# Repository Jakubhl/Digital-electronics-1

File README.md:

# Digital-electronics-1

## Labs

### Header3
~~Scratch this.~~
**Source code**

```vhdl
architecture dataflow of gates is
begin
  f_o <= ((not b_i) and a_i)or ((not c_i) and (not b_i));
  found_o <=
  --fand_o <= a_i and b_i;
  --fxor_o <= a_i xor b_i;
and architecture dataflow;
```
https://www.vutbr.cz/

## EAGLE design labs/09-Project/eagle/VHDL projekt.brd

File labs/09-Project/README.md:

# Parkovací asistent
[Odkaz na GitHub](https://github.com/Dan5049/DE1-project)

### Členové týmu
Fabula Boris      [GitHub](https://github.com/bfbl/Digital-electronics-1)  
Havránek Daniel   [GitHub](https://github.com/Dan5049/Digital-electronics-1)   
Hlaváček Jakub    [GitHub](https://github.com/Jakubhl/Digital-electronics-1)   
Horna Aleš        [GitHub](https://github.com/xhorna16/Digital-electronics-1)

### Cíl projektu
<br>

* Cílem projektu je vytvoření parkovacího asistentu. Základní verze obsahuje jeden ultrazvukový senzor HC-SR04, bargrafem realizovaným pomocí LED integrovaných na desce a zvukuvou signalizací pomocí bzučáku.
* V druhé verzi projektu je plánováno nahradit LED optickou signalizaci externího bargrafu.
* V třetí verzi projektu je plánováno použití třech ultrazvukových senzorů namísto jednoho. Pro optickou signalizaci bude za potřebí využít třech bargrafů - každý pro jeden senzor. Zvuková signalizace pomocí bzučáku bude poté pro nejkritičtejší hodnotu.

## Popis hardwaru
### Blokové schéma

<br>

Na blokovém schématu můžeme vidět princip fungování. *Clock generator* nám generuje hodinový signál o frekvenci 100MHz, který je přiváděn do bloku *Trigger generator* a *Distance counter*. Další vstup do obou bloků je *reset*. 

Blok *Trigger generator* generuje řídící signál pro senzor *HC-SR04*. Tento signál je 10μs v hodnotě 1 a poté v hodnotě 0. Perioda tohoto signálu je 100ms.

Výstup ze senzoru *HC-SR04* je přiváděn do bloku *Distance counter* jako signál *echo*. Podle délky tohoto signálu je zjištěna vzdálenost od objektu. Podle vzdálenosti od objektu se rozsvítí určitý počet LED a nastaví se délka pípání bzučáku.

<br>

### DPS
#### Schéma zapojení přídavné desky

#### Náhled desky

<br>

Blok optické a akustické signalisace
* bargraf s 10 LED se spojenými katodami je přes předřadné odpory připojen na příslušné výstupy FPGA
* samokmitající bzučák, napájený z 5V, je spínán tranzistorem MOSFET, ovládaným z výstupu FPGA
* dále jsou obsaženy dva převodníky úrovní mezi 3,3V a 5V využité pro komunikaci mezi FPGA a ultrazvukovým snímačem
Převodníky úrovní
* řeší problém odlišných napětí odpovídajících logickým úrovním 1 na hlavní desce (s FPGA) a ultrazvukovém snímači
* jako zdroje napětí 3,3V a 5V použijí se příslušné výstupy na hlavní desce
* přenáší úroveň z jedné strany na druhou činností tranzistoru MOSFET
* vstup pro úroveň s určitým napětím označen jako I3, resp. I5, podle napětí
* výstup pro úroveň s určitým napětím označen jako O3, resp. O5, podle napětí
* vysvětlení funkce na příkladu:
	* na I3 je úroveň log. 0 (0V), T1 je otevřen (UGS=3,3V), úroveň 0 se tak přenese na výstup O5, kde bude napětí blízké nule (T1 otevřen)
	* na I3 je úroveň log. 1 (3,3V), T1 je uzavřen (UGS=0V), úroveň 1 se tak přenese na výstup O5, kde bude napětí 5V (T1 uzavřen)
	* funkce druhého převodníku je analogická
Praktické provedení
* většina součástek v provedení SMD, odpory-1206, tranzistory-SOT23, přesné informace v souboru "seznam-soucastek.txt"
* tranzistory jsou MOSFET, typ 2N7002, prahové napětí UGSth, povolený proud ID a další parametry jsou postačující
* jednostranná DPS, připojení k hlavní desce realisuje se pomocí páskových vodičů pájených do DPS bloku signalisace, na straně desky s FPGA připojeny pomocí vhodného konektoru
* na DPS vyznačena místa pro vyvrtání otvorů pro eventuální uchycení 4 šrouby M3
* bargraf může být osazen do patice DIL, což usnadní případnou výměnu za jiný typ (jiná barva světla)

Seznam součástek a osazovací plány na desku jsou na gitu ve složce *eagle*, popřípadě ve složce *images*

## VHDL moduly a simulace
### Modul *trigger*
``` VHDL
library ieee;               -- Standard library
use ieee.std_logic_1164.all;-- Package for data types and logic operations
use ieee.numeric_std.all;   -- Package for arithmetic operations

entity trigger is
port(
    clk     : in std_logic;    --clock
    rst     : in std_logic;    --reset
    trig_o  : out std_logic);  --trigger signal to sonar
end entity trigger;

architecture Behavioral of trigger is 
    signal s_tick     : integer; --time counter, one tick is 10ns
begin

    p_trigger : process(clk)is
    begin
        if rising_edge(clk) then
            if rst = '1' then                                       --if reset is 1, set trigger and time counter to 0
                trig_o <= '0'; 
                s_tick <= 0;           
            else
                if (s_tick <= 1000) then                            --set trrigger to 1 for time equal to 1000 ticks (10us)
                    trig_o <= '1';
                    s_tick <= s_tick + 1;
                elsif (s_tick < 10000000 and s_tick >= 1000) then   --set trigger to 0 for the rest of the time of 100ms
                    s_tick <= s_tick + 1;
                    trig_o <= '0';
                else 
                    s_tick <= 0;                                    --reset time counting
                end if;
           end if;
       end if;
    end process p_trigger;
end architecture Behavioral;
```
Modul *trigger* slouží ke generování budícího signálu *trig_o* pro senzor *HC-SR04*. Pokud je *reset* v hodnotě 1, budící signál *trig_o* je nastavený na hodnotu 0. V opačném případě se počítá počet nástupných hran hodinového signálu *clk* a ukládá se do pomocného signálu *s_tick*. Podle hodnoty pomocného signálu *s_tick* se nastavuje hodnota budícího signálu *trig_o* do hodnoty 0 nebo 1.

Hodnota uložená v pomocném signálu *s_tick* je čas v desítkách nanosekund. Pokud je hodnota pomocného signálu *s_tick* menší než 1000 (10μs), tak je nastavena hodnota budícího signálu *s_trig* na hodnotu 1. V opačném případě je nastavena na hodnotu 0. Pokud je hodnota pomocného signálu *s_tick* větší než 10000000 (100ms), tak dojde k vynulování pomocného signálu *s_tick*.

#### Simulace triggru

<br>

### Modul *dist*
``` VHDL
library ieee;               -- Standard library
use ieee.std_logic_1164.all;-- Package for data types and logic operations
use ieee.numeric_std.all;   -- Package for arithmetic operations

entity dist is
port(
    clk       : in std_logic;
    rst       : in std_logic;
    echo_i    : in std_logic;  --input from sonar
    buzz_o    : out std_logic; --output to buzzer
    leds_o    : out std_logic_vector (10 - 1 downto 0));
end entity dist;

architecture Behavioral of dist is 
    signal s_tick     : integer; --auxiliary variable for time counting
    signal s_dist     : integer; --auxiliary variable for distance counting
    signal s_tock     : integer; --auxiliary variable for time counting
    signal s_tock_on  : integer; --duty cycle for PWM signal to buzzer
    signal s_tock_off : integer; --period of the PWM signal
    signal s_xyz      : std_logic := '1'; --echo rising edge detection signal
begin

    p_distance : process(clk, echo_i)is --measure distance 
    begin
        if rising_edge(clk) then
            if rst = '1' then
                s_dist <= 1000; -- if dist = 1000 - error value (10m - more than it's able to measure)
                s_tick <= 0;
            else
                if echo_i = '1' then -- if echo is on 1, start counting time
                    s_tick <= s_tick +1; 
                    s_dist <= s_tick /(100*58); --conversion of ticks to distnace
                else
                    s_tick <= 0;
                end if;
            end if;
        end if;
    end process p_distance;
    
    p_bargraf : process (echo_i, s_dist, s_xyz)  --set the number of leds and duty cycle of buzzer
    begin
        if s_dist > 400 then
            leds_o <= "0000000000";
            s_tock_on <= 0;
            s_tock_off <= 100000000;
        end if; 
        if s_xyz = '1' and echo_i = '0' then
            if (s_dist <= 400 and s_dist >= 150) then --distance 4m to 1.5m
                leds_o <= "0000000001";
                s_tock_on <= 3000000;
                s_tock_off <= 10000000;
            elsif (s_dist < 150 and s_dist >= 100) then --distance 1.5m to 1m
                leds_o <= "0000000011";
                s_tock_on <= 3500000;
                s_tock_off <= 10000000;
            elsif (s_dist < 100 and s_dist >= 80) then --distance 1m to 0.8m
                leds_o <= "0000000111";
                s_tock_on <= 4000000;
                s_tock_off <= 10000000;
            elsif (s_dist < 80 and s_dist >= 70) then --distance 0.8m to 0.7m
                leds_o <= "0000001111";
                s_tock_on <= 4500000;
                s_tock_off <= 10000000; 
            elsif (s_dist < 70 and s_dist >= 60) then --distance 0.7m to 0.6m
                leds_o <= "0000011111";
                s_tock_on <= 5000000;
                s_tock_off <= 10000000;
            elsif (s_dist < 60 and s_dist >= 50) then --distance 0.6m to 0.5m
                leds_o <= "0000111111";
                s_tock_on <= 6000000;
                s_tock_off <= 10000000;
            elsif (s_dist < 50 and s_dist >= 40) then --distance 0.5m to 0.4m
                leds_o <= "0001111111";
                s_tock_on <= 7000000;
                s_tock_off <= 10000000;
            elsif (s_dist < 40 and s_dist >= 35) then --distance 0.4m to 0.35m
                leds_o <= "0011111111";
                s_tock_on <= 8000000;
                s_tock_off <= 10000000;
            elsif (s_dist < 35 and s_dist >= 30) then --distance 0.35m to 0.3m
                leds_o <= "0111111111";
                s_tock_on <= 9000000;
                s_tock_off <= 10000000;
            elsif s_dist < 30 then                      --distance less than 0.3m
                leds_o <= "1111111111";
                s_tock_on <= 3000000;
                s_tock_off <= 0;
            else
                leds_o <= "0000000000";
                s_tock_on <= 0;
                s_tock_off <= 100000000;
            end if;
       end if;
       s_xyz <= echo_i;    
    end process p_bargraf;
    
    p_buzz : process(clk, s_tock, s_tock_on, s_tock_off, echo_i)is
    begin                           -- controll buzzer based on the duty cycle values from p_bargraf
        if rising_edge(clk) then
            if rst = '1' then
                buzz_o <= '0';
                s_tock <= 0;
            else                
                if (s_tock <= s_tock_on) then
                    buzz_o <= '1';
                    s_tock <= s_tock + 1;
                elsif (s_tock <= s_tock_off and s_tock >= s_tock_on) then
                    buzz_o <= '0';
                    s_tock <= s_tock + 1;
                else 
                    s_tock <= 0;
                end if;
            end if;
        end if;    
    end process p_buzz;
    
end architecture Behavioral;
```
Modul *dist* slouží k získání hodnoty vzdálenosti od objektu a následému ovládání výstupních signalizací. Skládá se ze tří procesů: *p_distance*, *p_bargraf* a *p_buzz*.

Proces *p_distance* měří délku signálu *echo_i* přicházejícího ze senzoru *HC-SR04*. Stejně jak v modulu *trigger* se měří délka signálu *echo_i* na základě počtu náběžných hran hodinového signálu *clk*. Pokud je tedy hodnota signálu *echo_i* v hodnotě 1, počítá se počet náběžných hran signálu *clk* a ukládá se do pomocného signálu *s_tick*, který je stejně jak předtím v desítkách nanosekudn. Pokud je reset v hodnotě 1, dojde k vyresetování celého procesu a vzdálenost, uložená v pomocném signálu *s_dist*, se nastaví na hodnotu 10000. Tato hodnota odpovídá vzdálenosti 10m, což je hodnota vyšší, než je senzor schopen měřit - errorová hodnota. Jinak dochází k přepočtu délky signálu *echo_i* na vzdálenost, která se následně ukládá do pomocného signálu *s_dist*. Přepočet je uveden v datasheetu k senzoru *HC-SR04* - čas v mikrosekudnách děleno 58 je roven vzdálenosti v centimetrech.

V procesu *p_bargraf* dochází k zapnutí určitého počtu LED, v závislosti na vzdálenosti (hodnota signálu *s_dist*). Počet rozsvícených LED není přímo úměrný vzdálenosti - pro větší vzdálenosti je odstup mezi jednotlivými LED větší než pro kratší vzdálenosti. Všechny LED svítí při vzdálenosti menší 30cm. Také se v tomto procesu nastavuje střída a perioda pro signál *s_buzz*, který spouští zvukovou signalizaci. Perioda signálu *s_buzz* je 100ms, střída se mění v závislosti na vzdálenosti a nastavuje se spolu s LED.

V procesu *p_buzz* dochází ke generování signálu pro zvukovou signalizaci *s_buzz* v závisloti na hodnotách získaných v předchozím procesu. Pokud je vzdálenost od objektu menší než 30cm, je signál *s_buzz* nastaven na hodnotu 1 a nemění se. Čím je vzdálenost větší, tím kratší dobu je signál *s_buzz* nastaven na hodnotu 1.

Ve složce *buzzer* je kód v matlabu, kterým jsme zjištovali minimální slyšitelnou délku pulzu. Z toho důvodu jsme se rozhodli nastavit nejkratší použitou časovou délku pulzu na 30ms.

#### Tabulka nastavení počtu LED a střídy bzučáku
| Vzdálenost [cm] | Počet LED | Střída [%] |
|:-:|:-:|:-:|
| nad 400 | 0 | 0 | 0 |
| 150 až 400 | 1 | 30 |
| 100 až 150 | 2 | 35 |
|  80 až 100 | 3 | 40 |
|  70 až  80 | 4 | 45 |
|  60 až  70 | 5 | 50 |
|  50 až  60 | 6 | 60 |
|  40 až  50 | 7 | 70 |
|  35 až  40 | 8 | 80 |
|  30 až  35 | 9 | 90 |
|  pod  30 | 10 | 100 |

<br>

#### Průběh simulace LED

<br>

#### Průběhy simulace bzučáku

## TOP modul a simulace

### Top modul kód
```VHDL
----------------------------------------------------------------------------------
-- Company: 
-- Engineer: 
-- 
-- Create Date: 20.04.2021 21:44:59
-- Design Name: 
-- Module Name: top - Behavioral
-- Project Name: 
-- Target Devices: 
-- Tool Versions: 
-- Description: 
-- 
-- Dependencies: 
-- 
-- Revision:
-- Revision 0.01 - File Created
-- Additional Comments:
-- 
----------------------------------------------------------------------------------

library IEEE;
use IEEE.STD_LOGIC_1164.ALL;

-- Uncomment the following library declaration if using
-- arithmetic functions with Signed or Unsigned values
--use IEEE.NUMERIC_STD.ALL;

-- Uncomment the following library declaration if instantiating
-- any Xilinx leaf cells in this code.
--library UNISIM;
--use UNISIM.VComponents.all;

entity top is
    port ( 
        CLK100MHZ   : in std_logic;
        btn         : in std_logic_vector (1 - 1 downto 0);
        ja          : out std_logic_vector(8 - 1 downto 0);
        jb          : out std_logic_vector (4 - 1 downto 0);
        jc          : in std_logic_vector(1 - 1 downto 0));
end top;

architecture Behavioral of top is
--no internal signals
begin
    
    trigger_top : entity work.trigger
        port map (
            clk         => CLK100MHZ,
            rst         => btn(0),
            trig_o      => ja(0));
            
    dist_top    : entity work.dist
        port map (
            clk                     => CLK100MHZ,
            rst                     => btn(0),  
            buzz_o                  => ja(1), 
            leds_o(6 - 1 downto 0)  => ja(8 - 1 downto 2),
            leds_o(10 - 1 downto 6) => jb(4 - 1 downto 0),
            echo_i                  => jc(0)); 
end Behavioral;
``` 

### Tabulka propojení
| **Signál**| **Výstupní pin** | **FPGA pin** | **FPGA package pin** |
| :-: | :-: | :-: | :-: |
| rst | btn[0] | IO_L6N_T0_VREF_16 | D9 |
| echo_i | jc[0] | IO_L20P_T3_A08_D24_14 | U12 |
| trig_o | ja[0] | IO_0_15 | G13 |
| buzz_o | ja[1] | IO_L4P_T0_15 | B11 |

<br>

### Tabulka propojení bragrafu
| **Signál -> leds_o**| **Výstupní pin** | **FPGA pin** | **FPGA package pin** |
| :-: | :-: | :-: | :-: |
| 0 | ja[2] | IO_L4N_T0_15 | A11 |
| 1 | ja[3] | IO_L6P_T0_15 | D12 |
| 2 | ja[4] | IO_L6N_T0_VREF_15 | D13 |
| 3 | ja[5] | IO_L10P_T1_AD11P_15 | B18 |
| 4 | ja[6] | IO_L10N_T1_AD11N_15 | A18 |
| 5 | ja[7] | IO_25_15 | K16 |
| 6 | jb[0] | IO_L11P_T1_SRCC_15 | E15 |
| 7 | jb[1] | IO_L11N_T1_SRCC_15 | E16 |
| 8 | jb[2] | IO_L12P_T1_MRCC_15 | D15 |
| 9 | jb[3] | IO_L12N_T1_MRCC_15 | C15 |

<br>

### Simulace topu

## Dosažené cíle
Povedlo se vytvořit parkovacího asistenta s jedním ultrazvukovým senzorem, zvukovou signalizací pomocí bzučáku a optickou signalizací pomocí bargrafu. Generování *triggrovacího* signálu a optická signalizace funguje bez problému. Při generování signálu pro bzučák se na počátku prvního *echa* oběví krátký pulz. Tento pulz je nechtěný, ale je tak krátky, že ho člověk není schopen zaregistrovat.

Projekt by se dal rozšířit přidáním dalších dvou ultrazvukových senzorů a bargrafů. Také by pro praktické použití na autě bylo vhodné vybrat jiný senzor (odolnější proti povětrnostním a pracovním podmínkám).

Projekt jsme také realizovali pomocí desky Arduino, stejného senzoru HC-SR04, bzučáku a čtyř ledek namísto bargrafu.

## Video
[Prezentacia projektu](https://drive.google.com/file/d/18ILoBno3hiMNqDnNoh6uOZaAPErlnejO/view?usp=sharing)
  
[Prezentacia na Arduine](https://drive.google.com/file/d/1YwLW6wj0uFljxe86JlJZtg1215zJ4bRm/view?usp=sharing)

## Reference
1. https://github.com/Digilent/digilent-xdc/blob/master/Arty-A7-100-Master.xdc
2. https://www.electroschematics.com/wp-content/uploads/2013/07/HCSR04-datasheet-version-1.pdf
3. https://github.com/tomas-fryza/Digital-electronics-1
4. https://app.diagrams.net/
5. https://vhdlwhiz.com/basic-vhdl-tutorials/

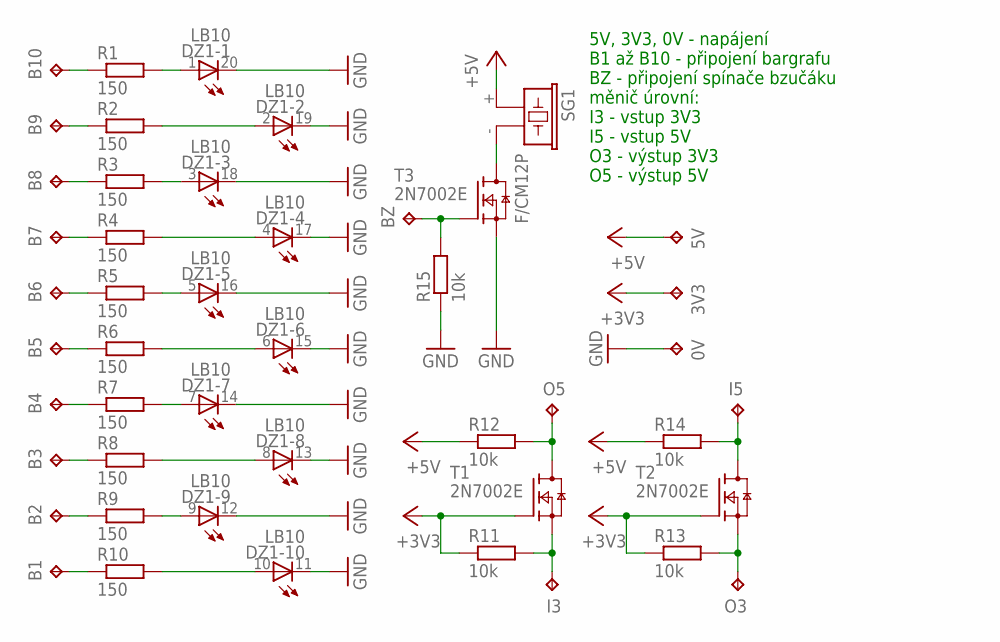
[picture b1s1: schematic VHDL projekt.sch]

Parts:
0V, 3V3, 5V: TPPAD1-13Y; P1-13Y
B1, B2, B3, B4, B5, B6, B7, B8, B9, B10: TPPAD1-13Y; P1-13Y
BZ: TPPAD1-13Y; P1-13Y
DZ1: LB10
I3, I5: TPPAD1-13Y; P1-13Y
O3, O5: TPPAD1-13Y; P1-13Y
R1, R2, R3, R4, R5, R6, R7, R8, R9, R10: 150; R1206
R11, R12, R13, R14, R15: 10k; R1206
SG1: F/CM12P
T1, T2, T3: 2N7002E; SOT23

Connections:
+3V3: 3V3.TP, R11.1, R13.1, T1.1 (G), T2.1 (G)
+5V: 5V.TP, R12.1, R14.1, SG1.+ (1)
GND: 0V.TP, DZ1.11 (C), DZ1.12 (C), DZ1.13 (C), DZ1.14 (C), DZ1.15 (C), DZ1.16 (C), DZ1.17 (C), DZ1.18 (C), DZ1.19 (C), DZ1.20 (C), R15.1, T3.2 (S)
unnamed: DZ1.1 (A), R1.2
unnamed: DZ1.2 (A), R2.2
unnamed: DZ1.3 (A), R3.2
unnamed: DZ1.4 (A), R4.2
unnamed: DZ1.5 (A), R5.2
unnamed: DZ1.6 (A), R6.2
unnamed: DZ1.7 (A), R7.2
unnamed: DZ1.8 (A), R8.2
unnamed: DZ1.9 (A), R9.2
unnamed: DZ1.10 (A), R10.2
unnamed: B10.TP, R1.1
unnamed: B9.TP, R2.1
unnamed: B8.TP, R3.1
unnamed: B7.TP, R4.1
unnamed: B6.TP, R5.1
unnamed: B5.TP, R6.1
unnamed: B4.TP, R7.1
unnamed: B3.TP, R8.1
unnamed: B2.TP, R9.1
unnamed: B1.TP, R10.1
unnamed: O5.TP, R12.2, T1.3 (D)
unnamed: I3.TP, R11.2, T1.2 (S)
unnamed: I5.TP, R14.2, T2.3 (D)
unnamed: O3.TP, R13.2, T2.2 (S)
unnamed: BZ.TP, R15.2, T3.1 (G)
unnamed: SG1.- (2), T3.3 (D)

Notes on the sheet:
5V, 3V3, 0V - napájení B1 až B10 - připojení bargrafu BZ - připojení spínače bzučáku měnič úrovní: I3 - vstup 3V3 I5 - vstup 5V O3 - výstup 3V3 O5 - výstup 5V

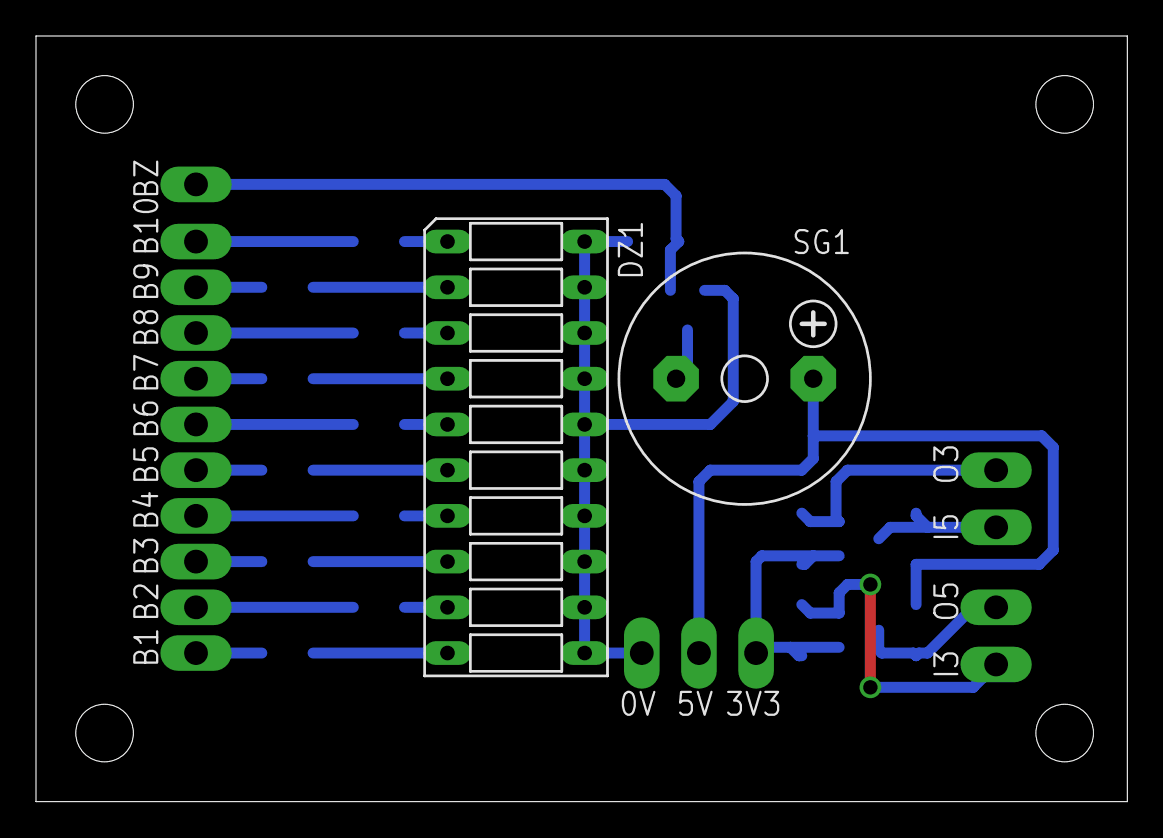
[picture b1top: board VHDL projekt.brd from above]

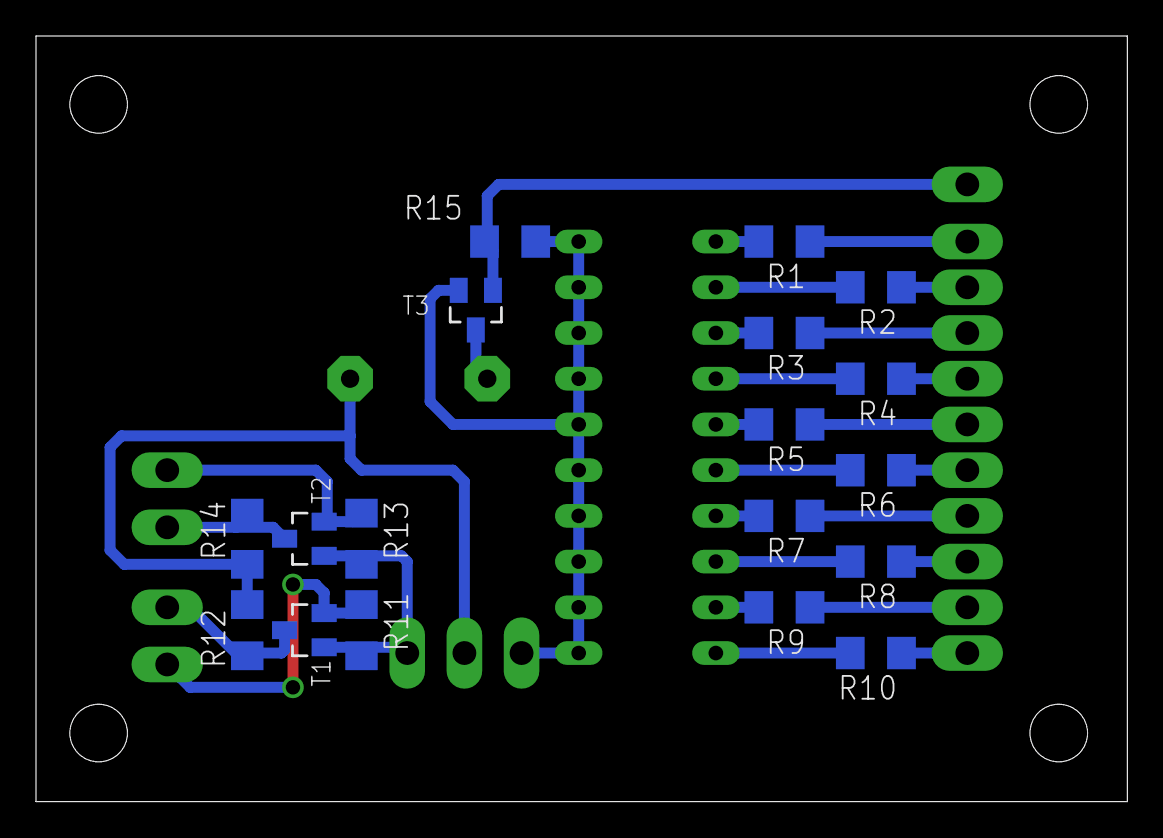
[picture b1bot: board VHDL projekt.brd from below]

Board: 2 copper layers, 60.6 x 42.5 mm, 38 parts (18 on the bottom side), 29 nets.

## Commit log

2021-02-15 splnil jsem bod 1
2021-02-15 pridana simulace
2021-02-15 ukladani obrazku
2021-02-15 rename
2021-02-17 Create labs-02_logic
2021-02-17 labs2
2021-02-17 pridani tabulky
2021-02-17 import obrázku
2021-02-24 pokus3
2021-03-03 update2
2021-03-24 Create 07-ffs
2021-03-24 Update 07-ffs
2021-05-02 Create project
